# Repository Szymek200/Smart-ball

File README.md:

# ⚽ SmartBall: IoT Sports Training System

SmartBall is a comprehensive hardware and software solution designed to enhance sports training by monitoring ball dynamics in real-time. The system focuses on tracking impact force and spin (angular velocity), providing athletes with immediate feedback on their performance.

This project was developed as part of the "Microprocessor and Embedded Systems" course at the Silesian University of Technology (Politechnika Śląska).

## 📂 Repository Structure

This repository is organized into three specialized modules. For detailed technical instructions and implementation logic, please refer to the documentation within each folder:

* **/mobile-app** – Android application (Kotlin) for real-time UDP data visualization, session history, and remote sensor configuration.
* **/firmware-esp32** – ESP-IDF C code featuring high-G impact detection, quaternion-based sensor fusion (complementary filter), and power management.
* **/hardware-3d** – 3D enclosure designs (PET-G), PCB schematics, and the Bill of Materials (BOM).

## ⚙️ System Architecture

The system utilizes a **Producer-Consumer** architecture to ensure high performance and low latency:

* **The Producer (ESP32):** Equipped with an **H3LIS331DL** (400g accelerometer) and an **L3G4200D** (2000 dps gyroscope). It processes raw motion data, compensates for gravity using quaternions, and detects strikes using a circular buffer to capture pre-impact telemetry.
* **The Consumer (Mobile App):** Connects to the ball via a Wi-Fi Access Point and receives processed statistics and live streams using a high-speed binary UDP protocol.

## 🚀 Quick Start Guide

1.  **Power On:** Ensure the Li-Pol battery is charged and the device is powered.
2.  **Connect Wi-Fi:** On your mobile device, connect to the SmartBall network:
    * **SSID:** `SmartBall_ESP32`
    * **Password:** `12345678`
3.  **Launch Application:** Open the SmartBall app to begin receiving data.
4.  **Analyze:** Use the "History" section to view detailed charts of every kick, including G-force and rotation speed.

## 🔋 Power Management

To maximize the 18-hour battery life, the system includes an automated Power Management Algorithm:
* **Deep Sleep:** The MCU enters deep sleep after a configurable period of inactivity.
* **Motion Wake-up:** The accelerometer remains active as a low-power motion detector, waking the ESP32 via a hardware interrupt (GPIO 32) when the ball is moved.

## 🛠 Tech Stack Summary

* **Microcontroller:** ESP32-WROOM-32 (Dual-core).
* **Firmware:** ESP-IDF (C), FreeRTOS, LwIP (UDP).
* **Mobile App:** Kotlin, Coroutines, MPAndroidChart.
* **Mechanical:** 3D Printed PET-G, Li-Pol 1580mAh, MP2636 Power Manager.

---
*Developed by Szymon Mamok | Silesian University of Technology 2025/2026*

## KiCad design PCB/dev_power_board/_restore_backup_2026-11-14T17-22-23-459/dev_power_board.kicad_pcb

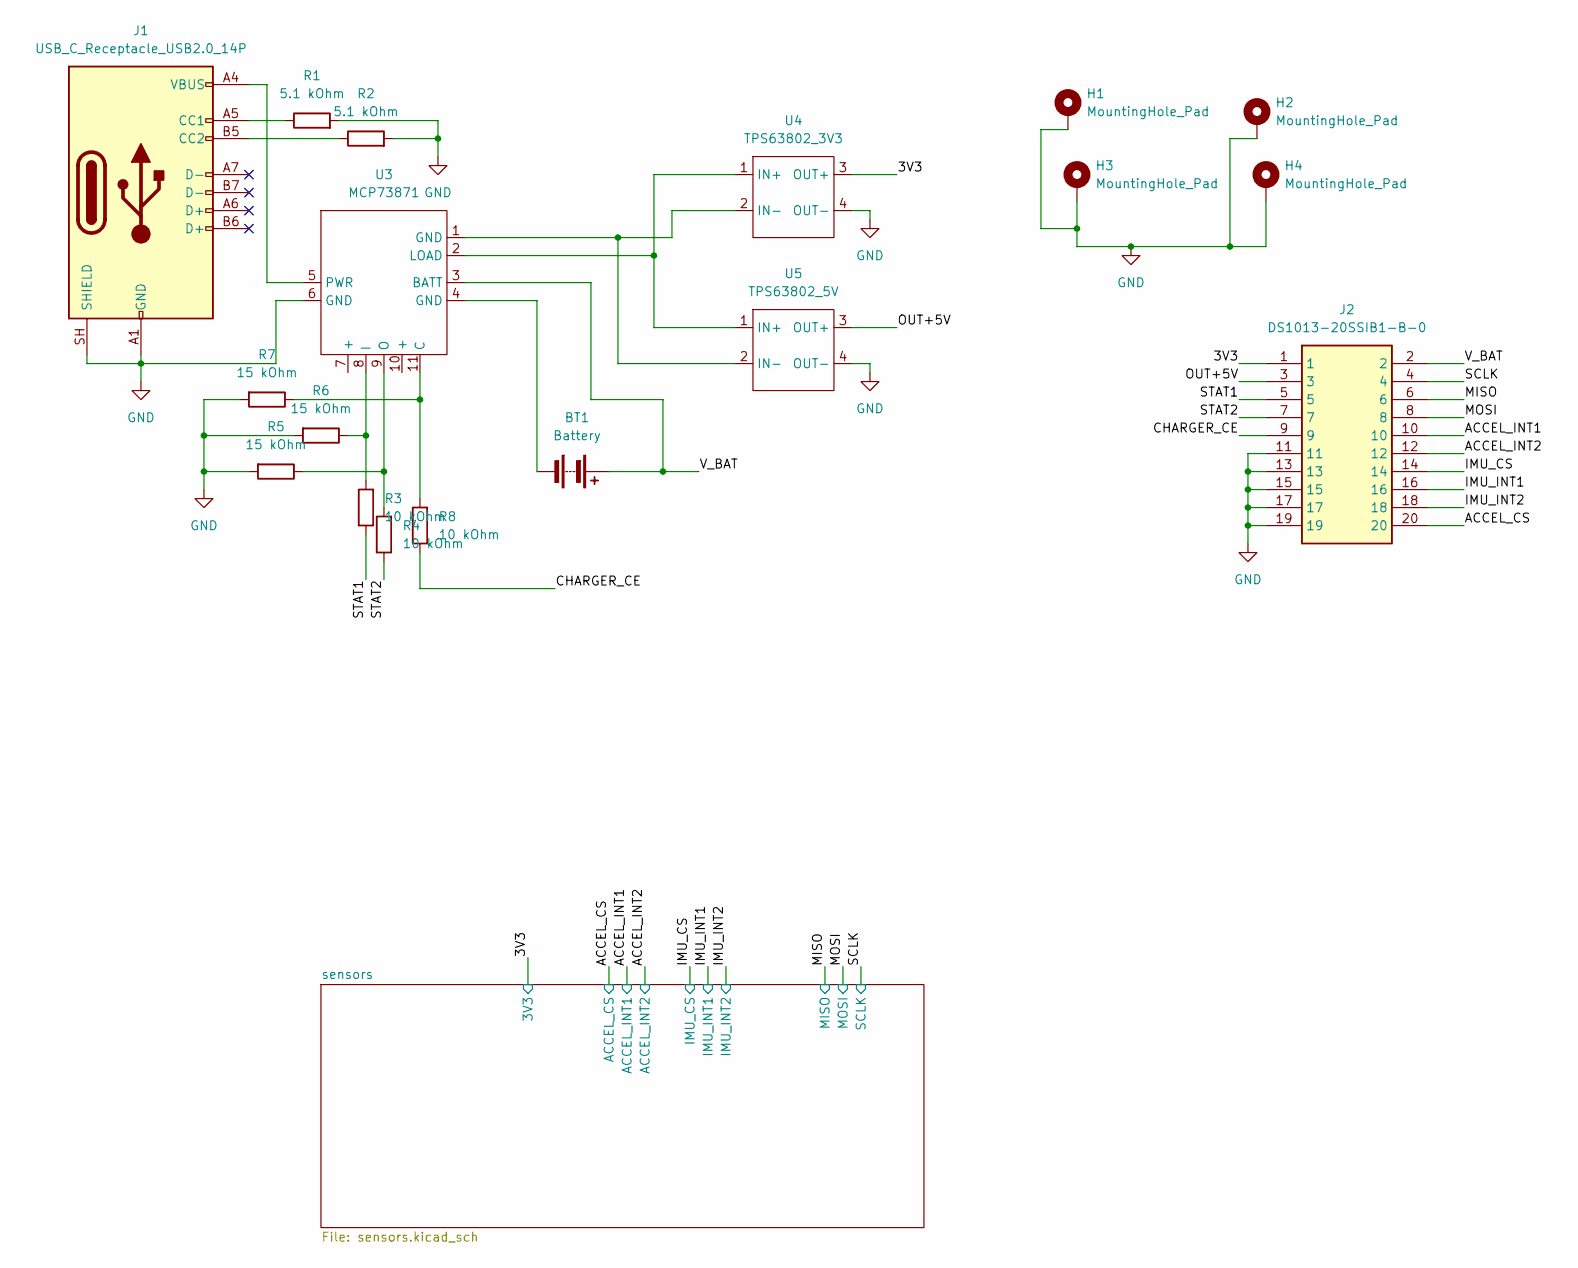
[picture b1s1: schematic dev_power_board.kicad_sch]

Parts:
BT1: Battery; PinHeader_1x02_P2.54mm_Vertical
H1, H2, H3, H4: MountingHole_Pad; MountingHole_2.2mm_M2_Pad
J1: USB_C_Receptacle_USB2.0_14P; USB_C_Receptacle_HRO_TYPE-C-31-M-12
J2: DS1013-20SSIB1-B-0; SHDR20W69P254X254_2X10_3300X910X955P; Manufacturer_Part_Number DS1013-20SSIB1-B-0
R1, R2: 5.1 kOhm; R_Axial_DIN0207_L6.3mm_D2.5mm_P7.62mm_Horizontal
R3, R4, R8: 10 kOhm; R_Axial_DIN0207_L6.3mm_D2.5mm_P7.62mm_Horizontal
R5, R6, R7: 15 kOhm; R_Axial_DIN0207_L6.3mm_D2.5mm_P7.62mm_Horizontal
U3: MCP73871; MCP73871_dev
U4: TPS63802_3V3; TPS63802_dev
U5: TPS63802_5V; TPS63802_dev

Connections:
/3V3: J2.1, U4.3 (OUT+); also elsewhere on the board
/ACCEL_CS: J2.20; also elsewhere on the board
/ACCEL_INT1: J2.10; also elsewhere on the board
/ACCEL_INT2: J2.12; also elsewhere on the board
/CHARGER_CE: J2.9, R8.1
/IMU_CS: J2.14; also elsewhere on the board
/IMU_INT1: J2.16; also elsewhere on the board
/IMU_INT2: J2.18; also elsewhere on the board
/MISO: J2.6; also elsewhere on the board
/MOSI: J2.8; also elsewhere on the board
/OUT+5V: J2.3, U5.3 (OUT+)
/SCLK: J2.4; also elsewhere on the board
/STAT1: J2.5, R3.1
/STAT2: J2.7, R4.1
/V_BAT: BT1.1 (+), J2.2, U3.3 (BATT)
GND: H1.1 (1_1), H2.1 (1_1), H3.1 (1_1), H4.1 (1_1), J1.A1 (GND), J1.A12 (GND), J1.B1 (GND), J1.B12 (GND), J1.SH (SHIELD), J2.11, J2.13, J2.15, J2.17, J2.19, R1.2, R2.2, R5.2, R6.2, R7.2, U3.6 (GND), U4.4 (OUT-), U5.4 (OUT-); also elsewhere on the board
unnamed: BT1.2 (-), U3.4 (GND)
unnamed: J1.A5 (CC1), R1.1
unnamed: J1.B5 (CC2), R2.1
unnamed: R7.1, R8.2, U3.11 (C)
unnamed: R3.2, R6.1, U3.8 (I)
unnamed: U3.2 (LOAD), U4.1 (IN+), U5.1 (IN+)
unnamed: R4.2, R5.1, U3.9 (O)
unnamed: J1.A4 (VBUS), J1.A9 (VBUS), J1.B4 (VBUS), J1.B9 (VBUS), U3.5 (PWR)
unnamed: U3.1 (GND), U4.2 (IN-), U5.2 (IN-)

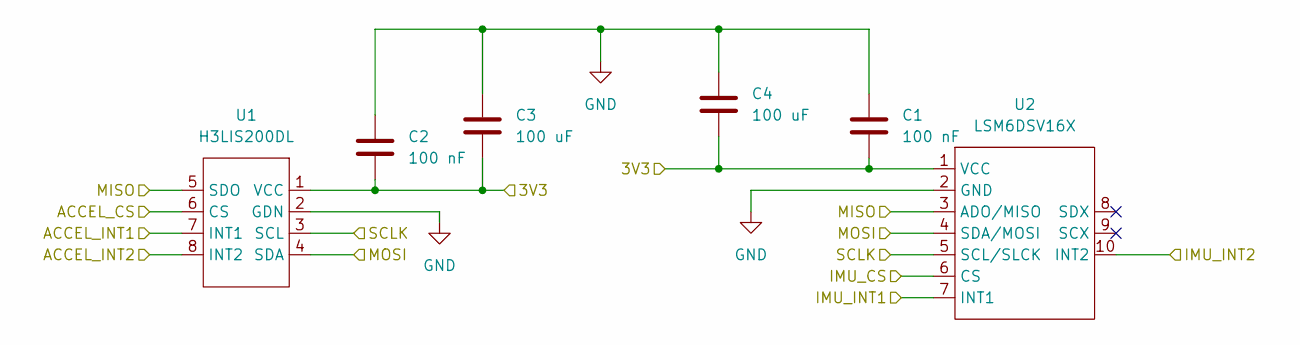
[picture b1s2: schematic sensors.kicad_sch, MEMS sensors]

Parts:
C1, C2: 100 nF; C_Disc_D5.0mm_W2.5mm_P5.00mm
C3, C4: 100 uF; CP_Radial_D6.3mm_P2.50mm
U1: H3LIS200DL; H3LIS200DL_dev
U2: LSM6DSV16X; LSM6DSV16X_dev

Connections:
/3V3: C1.2, C2.2, C3.1, C4.1, U1.1 (VCC), U2.1 (VCC); also elsewhere on the board
/ACCEL_CS: U1.6 (CS); also elsewhere on the board
/ACCEL_INT1: U1.7 (INT1); also elsewhere on the board
/ACCEL_INT2: U1.8 (INT2); also elsewhere on the board
/IMU_CS: U2.6 (CS); also elsewhere on the board
/IMU_INT1: U2.7 (INT1); also elsewhere on the board
/IMU_INT2: U2.10 (INT2); also elsewhere on the board
/MISO: U1.5 (SDO), U2.3 (ADO/MISO); also elsewhere on the board
/MOSI: U1.4 (SDA), U2.4 (SDA/MOSI); also elsewhere on the board
/SCLK: U1.3 (SCL), U2.5 (SCL/SLCK); also elsewhere on the board
GND: C1.1, C2.1, C3.2, C4.2, U1.2 (GDN), U2.2 (GND); also elsewhere on the board

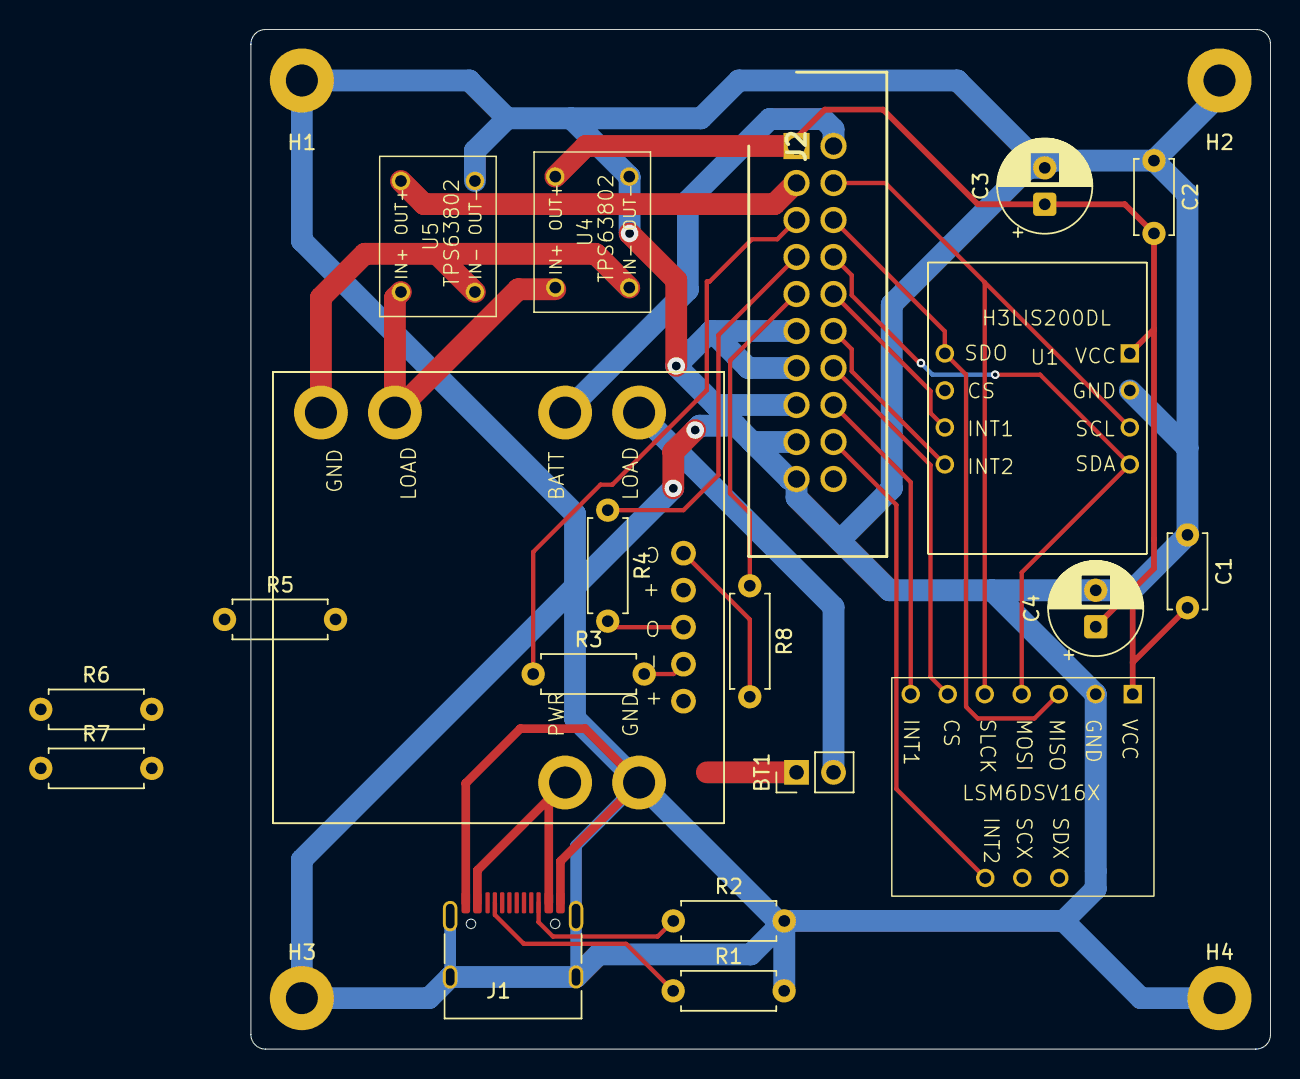
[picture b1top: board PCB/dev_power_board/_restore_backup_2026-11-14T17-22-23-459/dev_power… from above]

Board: 2 copper layers, 70.0 x 70.0 mm, 24 parts (0 on the bottom side), 25 nets.

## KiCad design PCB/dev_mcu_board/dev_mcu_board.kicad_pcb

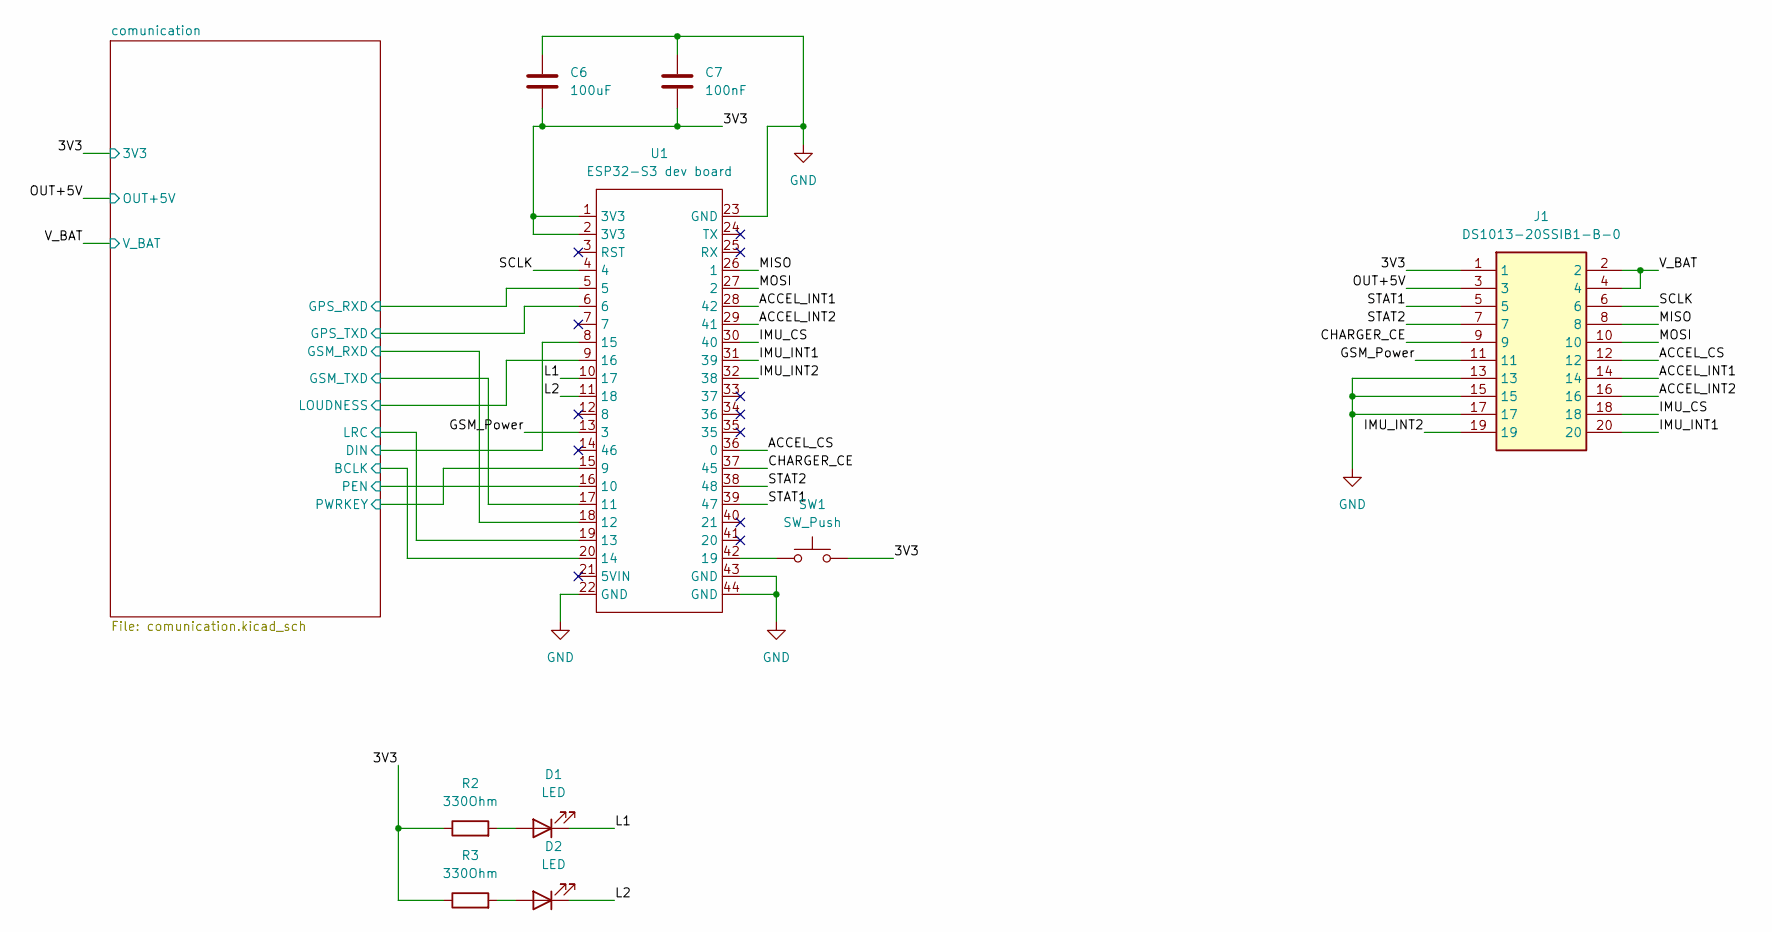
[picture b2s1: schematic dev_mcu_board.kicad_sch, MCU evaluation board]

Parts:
C6: 100uF; CP_Radial_D6.3mm_P2.50mm
C7: 100nF; C_Disc_D5.0mm_W2.5mm_P5.00mm
D1, D2: LED; LED_D5.0mm
J1: DS1013-20SSIB1-B-0; SHDR20W69P254X254_2X10_3300X910X955P; Manufacturer_Part_Number DS1013-20SSIB1-B-0
R2, R3: 330Ohm; R_Axial_DIN0207_L6.3mm_D2.5mm_P7.62mm_Horizontal
SW1: SW_Push; push_button
U1: ESP32-S3 dev board; esp32-s3_dev

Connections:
/3V3: C6.1, C7.2, J1.1, R2.1, R3.1, SW1.2, U1.1 (3V3), U1.2 (3V3); also elsewhere on the board
/ACCEL_CS: J1.12, U1.36 (0)
/ACCEL_INT1: J1.14, U1.28 (42)
/ACCEL_INT2: J1.16, U1.29 (41)
/CHARGER_CE: J1.9, U1.37 (45)
/GSM_Power: J1.11, U1.13 (3)
/IMU_CS: J1.18, U1.30 (40)
/IMU_INT1: J1.20, U1.31 (39)
/IMU_INT2: J1.19, U1.32 (38)
/L1: D1.1 (K), U1.10 (17)
/L2: D2.1 (K), U1.11 (18)
/MISO: J1.8, U1.26 (1)
/MOSI: J1.10, U1.27 (2)
/OUT+5V: J1.3; also elsewhere on the board
/SCLK: J1.6, U1.4
/STAT1: J1.5, U1.39 (47)
/STAT2: J1.7, U1.38 (48)
/V_BAT: J1.2, J1.4; also elsewhere on the board
/comunication/BCLK: U1.20 (14); also elsewhere on the board
/comunication/DIN: U1.8 (15); also elsewhere on the board
/comunication/GPS_RXD: U1.5; also elsewhere on the board
/comunication/GPS_TXD: U1.6; also elsewhere on the board
/comunication/GSM_RXD: U1.18 (12); also elsewhere on the board
/comunication/GSM_TXD: U1.17 (11); also elsewhere on the board
/comunication/LOUDNESS: U1.9 (16); also elsewhere on the board
/comunication/LRC: U1.19 (13); also elsewhere on the board
/comunication/PEN: U1.16 (10); also elsewhere on the board
/comunication/PWRKEY: U1.15 (9); also elsewhere on the board
GND: C6.2, C7.1, J1.13, J1.15, J1.17, U1.22 (GND), U1.23 (GND), U1.43 (GND), U1.44 (GND); also elsewhere on the board
unnamed: D1.2 (A), R2.2
unnamed: D2.2 (A), R3.2
unnamed: SW1.1, U1.42 (19)

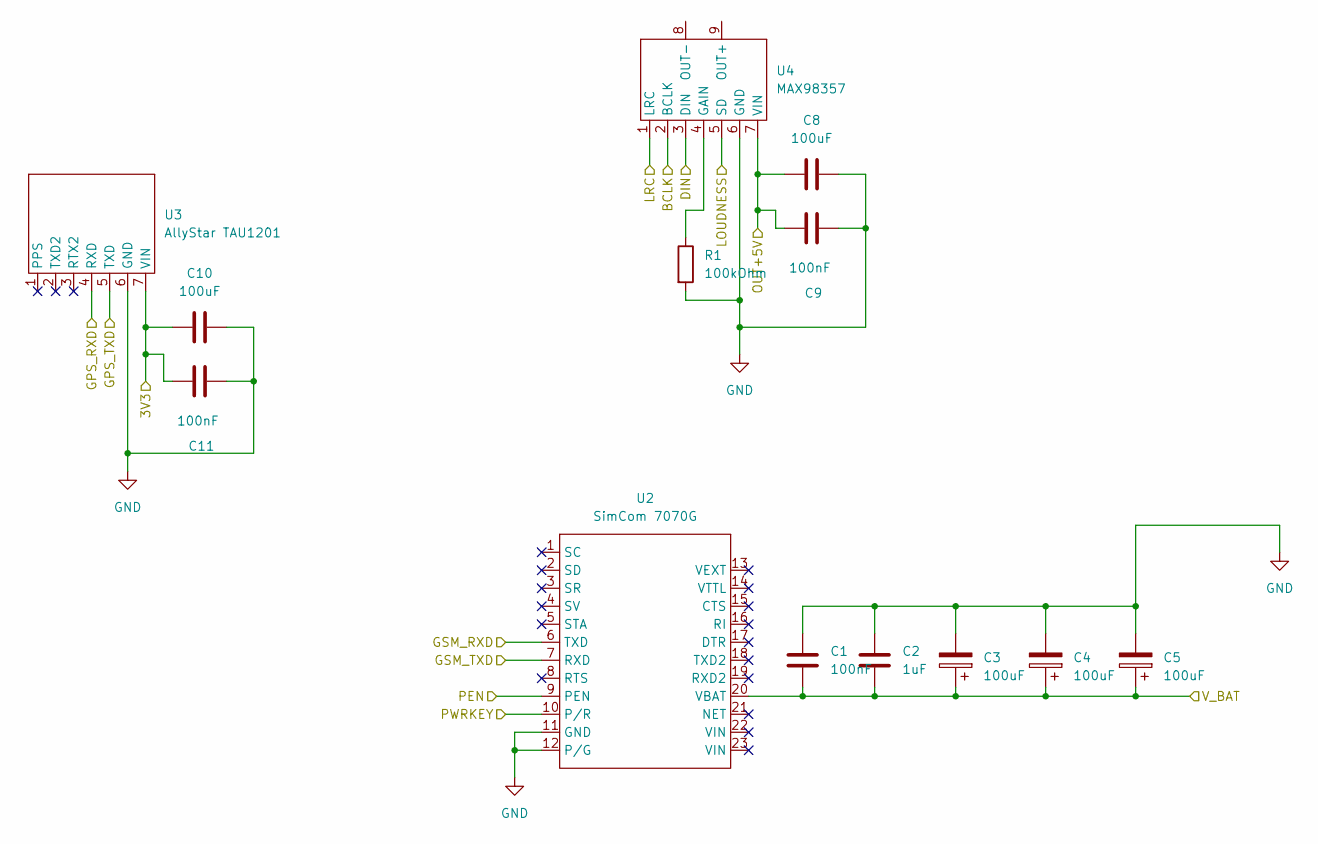
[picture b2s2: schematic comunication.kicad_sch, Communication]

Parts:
C1, C9, C11: 100nF; C_Disc_D5.0mm_W2.5mm_P5.00mm
C2: 1uF; CP_Radial_D5.0mm_P2.00mm
C3, C4, C5, C8, C10: 100uF; CP_Radial_D6.3mm_P2.50mm
R1: 100kOhm; R_Axial_DIN0207_L6.3mm_D2.5mm_P7.62mm_Horizontal
U2: SimCom 7070G; sim7070G_dev
U3: AllyStar TAU1201; TAU1201_dev
U4: MAX98357; MAX98357_dev

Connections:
/3V3: C10.1, C11.1, U3.7 (VIN); also elsewhere on the board
/OUT+5V: C8.1, C9.1, U4.7 (VIN); also elsewhere on the board
/V_BAT: C1.2, C2.1, C3.1, C4.1, C5.1, U2.20 (VBAT); also elsewhere on the board
/comunication/BCLK: U4.2 (BCLK); also elsewhere on the board
/comunication/DIN: U4.3 (DIN); also elsewhere on the board
/comunication/GPS_RXD: U3.4 (RXD); also elsewhere on the board
/comunication/GPS_TXD: U3.5 (TXD); also elsewhere on the board
/comunication/GSM_RXD: U2.6 (TXD); also elsewhere on the board
/comunication/GSM_TXD: U2.7 (RXD); also elsewhere on the board
/comunication/LOUDNESS: U4.5 (SD); also elsewhere on the board
/comunication/LRC: U4.1 (LRC); also elsewhere on the board
/comunication/PEN: U2.9 (PEN); also elsewhere on the board
/comunication/PWRKEY: U2.10 (P/R); also elsewhere on the board
GND: C1.1, C2.2, C3.2, C4.2, C5.2, C8.2, C9.2, C10.2, C11.2, R1.2, U2.11 (GND), U2.12 (P/G), U3.6 (GND), U4.6 (GND); also elsewhere on the board
unnamed: R1.1, U4.4 (GAIN)

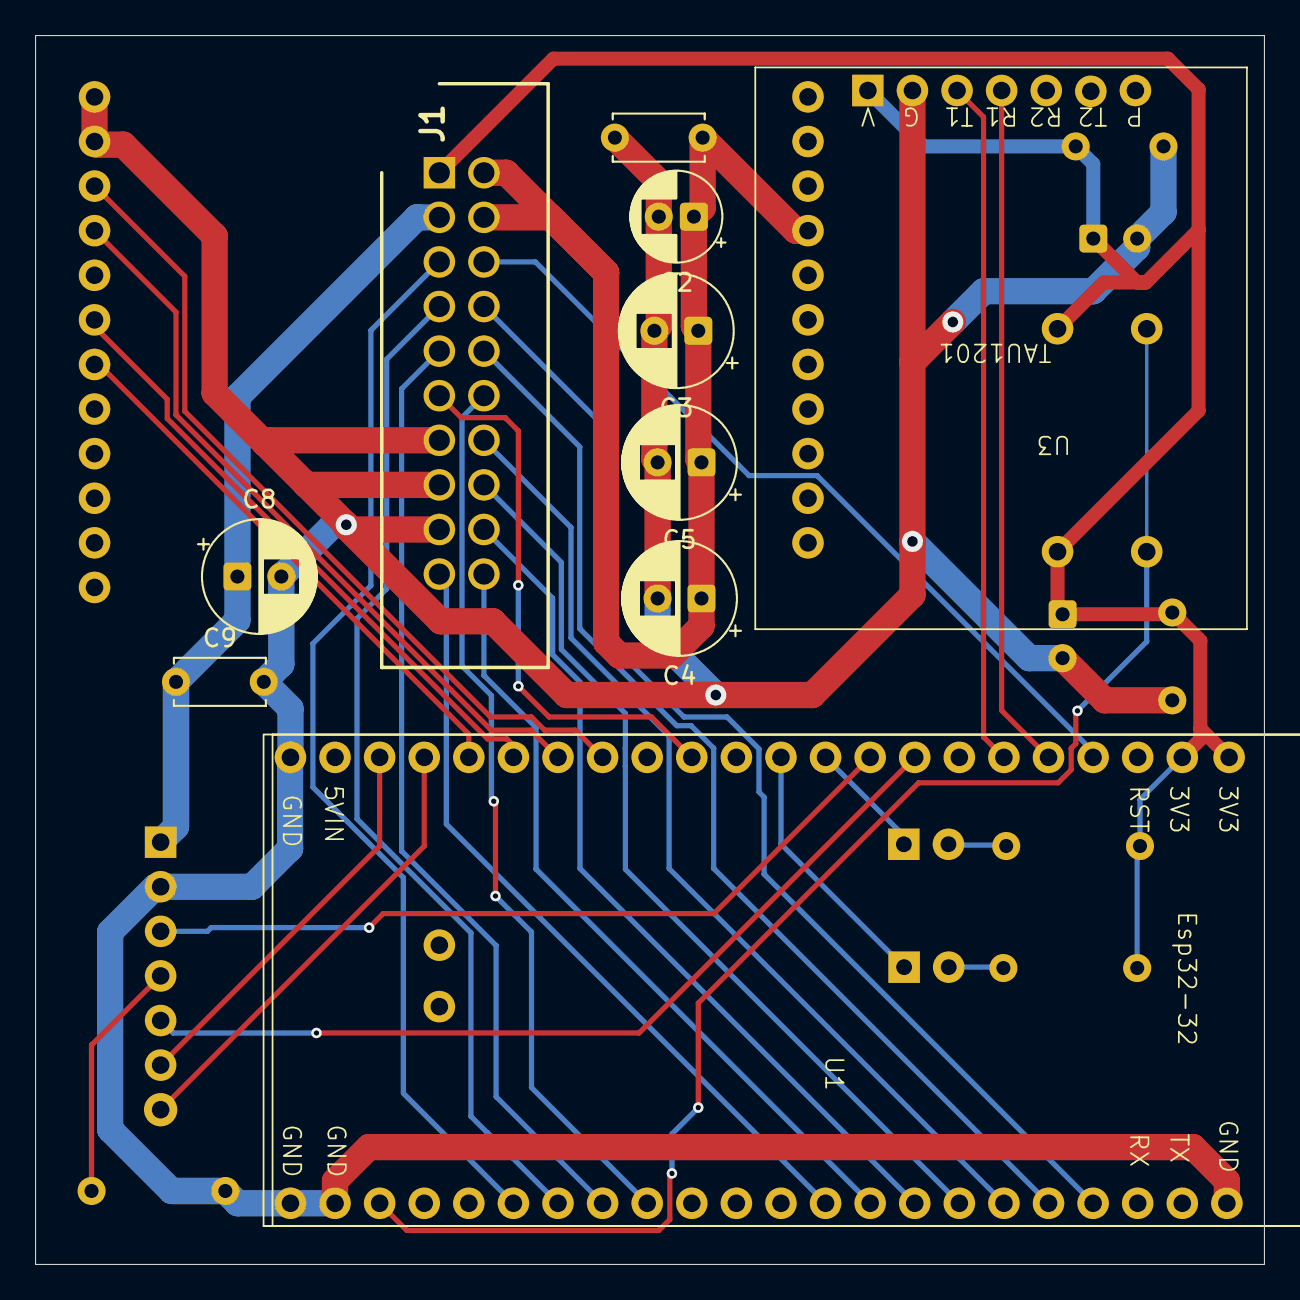
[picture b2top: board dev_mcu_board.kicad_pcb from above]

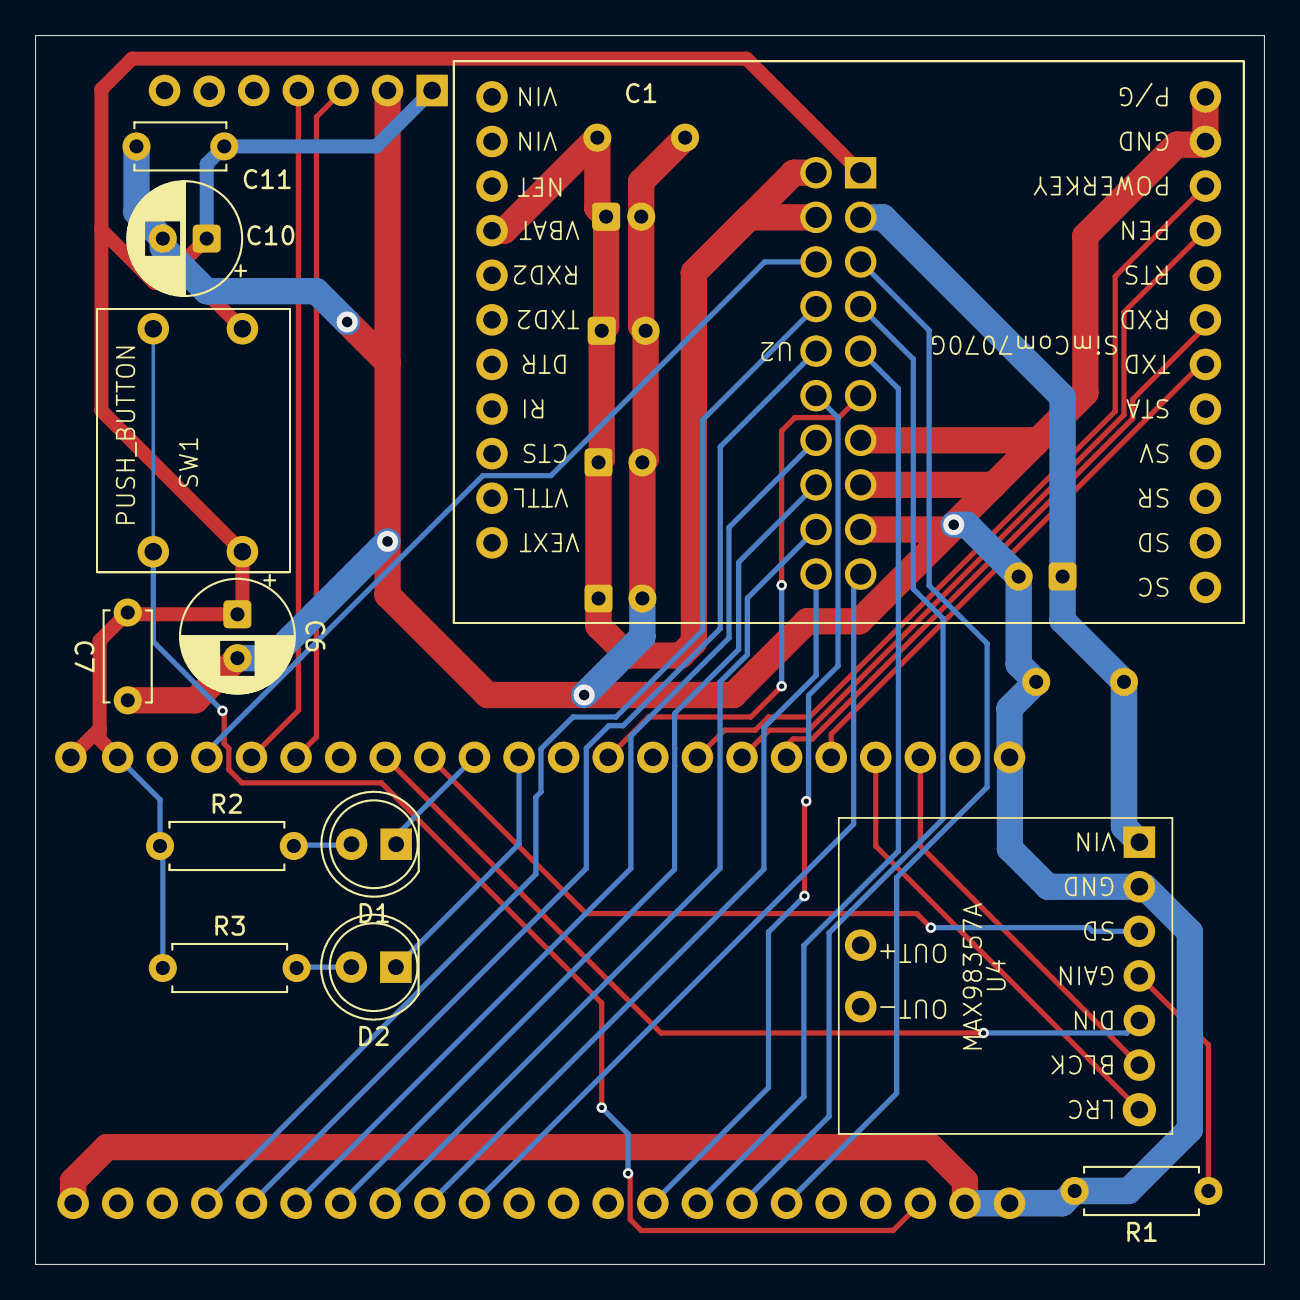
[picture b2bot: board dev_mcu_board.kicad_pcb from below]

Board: 2 copper layers, 70.0 x 70.0 mm, 22 parts (12 on the bottom side), 33 nets.

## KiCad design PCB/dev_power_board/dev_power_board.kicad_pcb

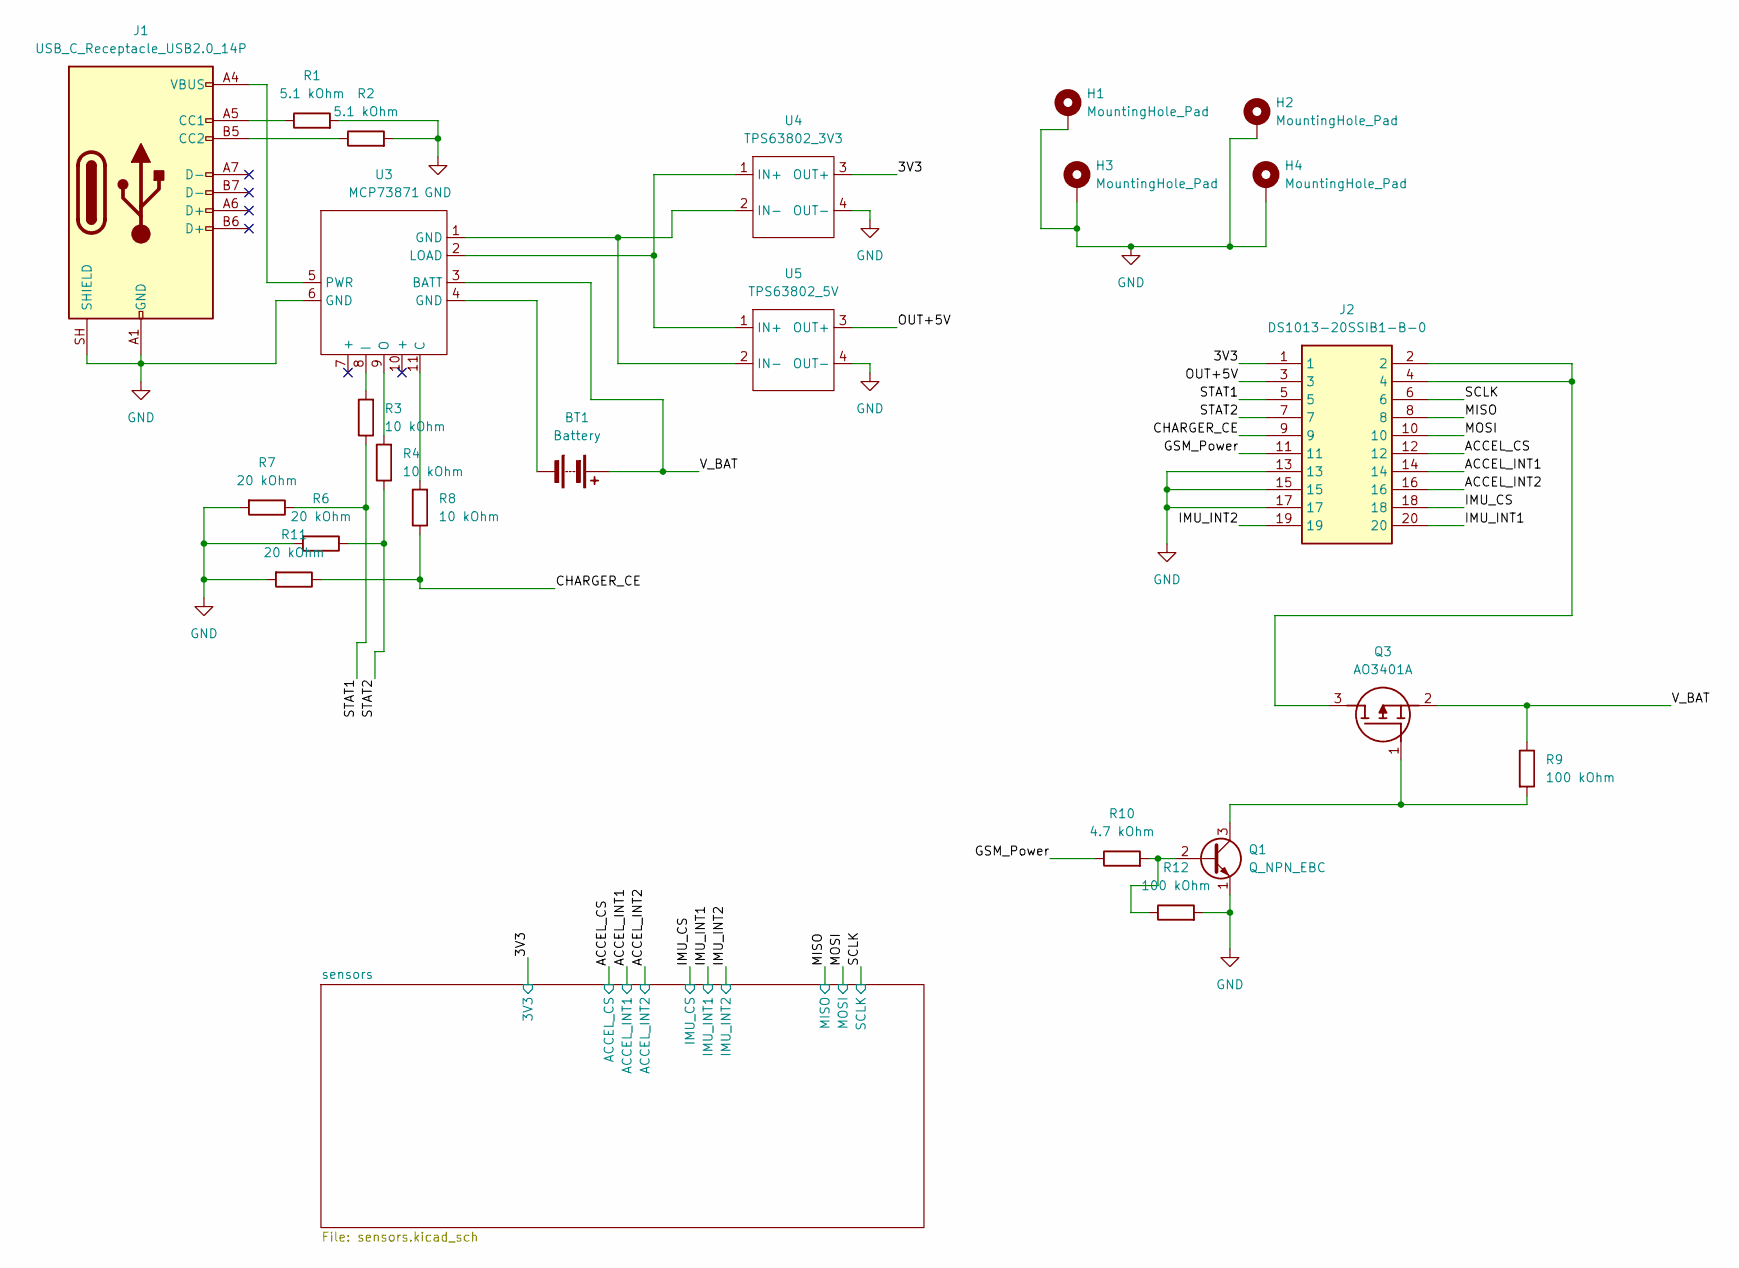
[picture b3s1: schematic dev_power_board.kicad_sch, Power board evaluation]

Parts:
BT1: Battery; PinHeader_1x02_P2.54mm_Vertical
H1, H2, H3, H4: MountingHole_Pad; MountingHole_2.2mm_M2_Pad
J1: USB_C_Receptacle_USB2.0_14P; USB_C_Receptacle_HRO_TYPE-C-31-M-12
J2: DS1013-20SSIB1-B-0; SHDR20W69P254X254_2X10_3300X910X955P; Manufacturer_Part_Number DS1013-20SSIB1-B-0
Q1: Q_NPN_EBC; TO-92_Wide
Q3: AO3401A; SOT95P280X125-3N; Manufacturer_Part_Number AO3401A
R1, R2: 5.1 kOhm; R_Axial_DIN0207_L6.3mm_D2.5mm_P7.62mm_Horizontal
R3, R4, R8: 10 kOhm; R_Axial_DIN0207_L6.3mm_D2.5mm_P7.62mm_Horizontal
R6, R7, R11: 20 kOhm; R_Axial_DIN0207_L6.3mm_D2.5mm_P7.62mm_Horizontal
R9, R12: 100 kOhm; R_Axial_DIN0207_L6.3mm_D2.5mm_P7.62mm_Horizontal
R10: 4.7 kOhm; R_Axial_DIN0207_L6.3mm_D2.5mm_P7.62mm_Horizontal
U3: MCP73871; MCP73871_dev
U4: TPS63802_3V3; TPS63802_dev
U5: TPS63802_5V; TPS63802_dev

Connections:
/3V3: J2.1, U4.3 (OUT+); also elsewhere on the board
/ACCEL_CS: J2.12; also elsewhere on the board
/ACCEL_INT1: J2.14; also elsewhere on the board
/ACCEL_INT2: J2.16; also elsewhere on the board
/CHARGER_CE: J2.9, R8.1, R11.1
/GSM_Power: J2.11, R10.1
/IMU_CS: J2.18; also elsewhere on the board
/IMU_INT1: J2.20; also elsewhere on the board
/IMU_INT2: J2.19; also elsewhere on the board
/MISO: J2.8; also elsewhere on the board
/MOSI: J2.10; also elsewhere on the board
/OUT+5V: J2.3, U5.3 (OUT+)
/SCLK: J2.6; also elsewhere on the board
/STAT1: J2.5, R3.1, R7.1
/STAT2: J2.7, R4.1, R6.1
/V_BAT: BT1.1 (+), Q3.2 (S), R9.1, U3.3 (BATT)
GND: H1.1 (1_1), H2.1 (1_1), H3.1 (1_1), H4.1 (1_1), J1.A1 (GND), J1.A12 (GND), J1.B1 (GND), J1.B12 (GND), J1.SH (SHIELD), J2.13, J2.15, J2.17, Q1.1 (E), R1.2, R2.2, R6.2, R7.2, R11.2, R12.2, U3.6 (GND), U4.4 (OUT-), U5.4 (OUT-); also elsewhere on the board
unnamed: BT1.2 (-), U3.4 (GND)
unnamed: J1.A5 (CC1), R1.1
unnamed: J1.B5 (CC2), R2.1
unnamed: Q1.2 (B), R10.2, R12.1
unnamed: Q1.3 (C), Q3.1 (G), R9.2
unnamed: J2.2, J2.4, Q3.3 (D)
unnamed: R8.2, U3.11 (C)
unnamed: R3.2, U3.8 (I)
unnamed: U3.2 (LOAD), U4.1 (IN+), U5.1 (IN+)
unnamed: R4.2, U3.9 (O)
unnamed: J1.A4 (VBUS), J1.A9 (VBUS), J1.B4 (VBUS), J1.B9 (VBUS), U3.5 (PWR)
unnamed: U3.1 (GND), U4.2 (IN-), U5.2 (IN-)

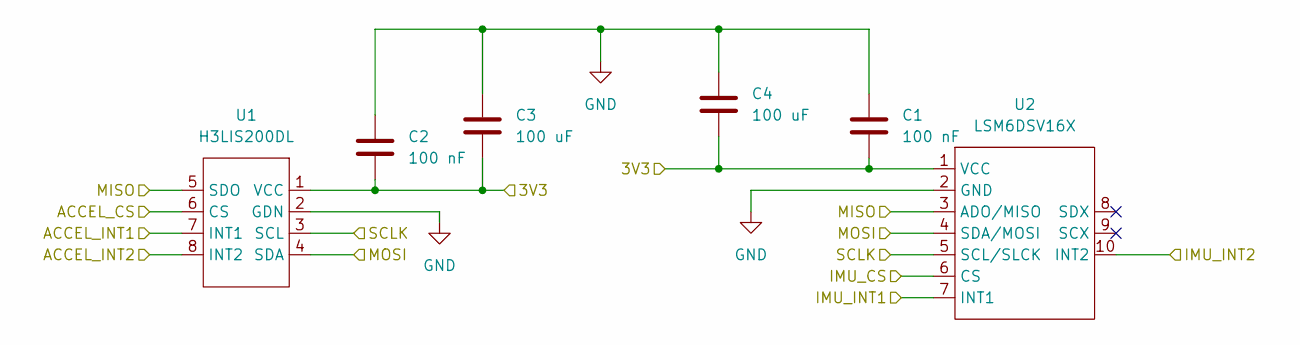
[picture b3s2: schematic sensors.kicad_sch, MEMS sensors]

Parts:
C1, C2: 100 nF; C_Disc_D5.0mm_W2.5mm_P5.00mm
C3, C4: 100 uF; CP_Radial_D6.3mm_P2.50mm
U1: H3LIS200DL; H3LIS200DL_dev
U2: LSM6DSV16X; LSM6DSV16X_dev

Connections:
/3V3: C1.2, C2.2, C3.1, C4.1, U1.1 (VCC), U2.1 (VCC); also elsewhere on the board
/ACCEL_CS: U1.6 (CS); also elsewhere on the board
/ACCEL_INT1: U1.7 (INT1); also elsewhere on the board
/ACCEL_INT2: U1.8 (INT2); also elsewhere on the board
/IMU_CS: U2.6 (CS); also elsewhere on the board
/IMU_INT1: U2.7 (INT1); also elsewhere on the board
/IMU_INT2: U2.10 (INT2); also elsewhere on the board
/MISO: U1.5 (SDO), U2.3 (ADO/MISO); also elsewhere on the board
/MOSI: U1.4 (SDA), U2.4 (SDA/MOSI); also elsewhere on the board
/SCLK: U1.3 (SCL), U2.5 (SCL/SLCK); also elsewhere on the board
GND: C1.1, C2.1, C3.2, C4.2, U1.2 (GDN), U2.2 (GND); also elsewhere on the board

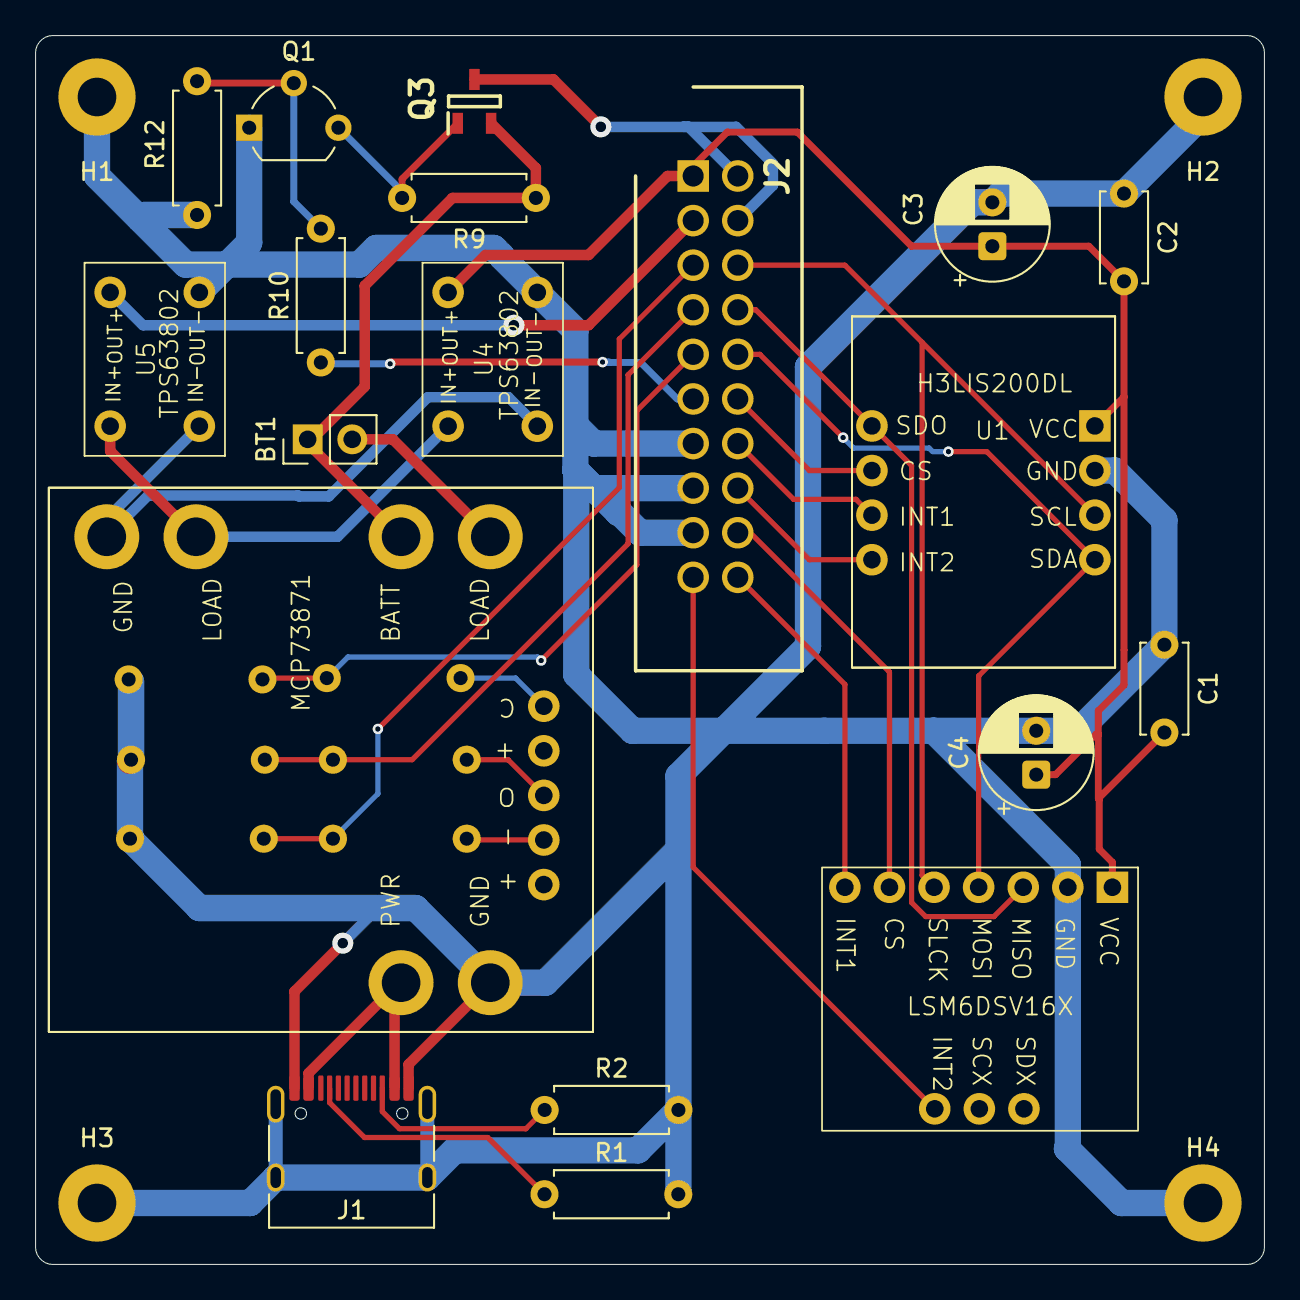
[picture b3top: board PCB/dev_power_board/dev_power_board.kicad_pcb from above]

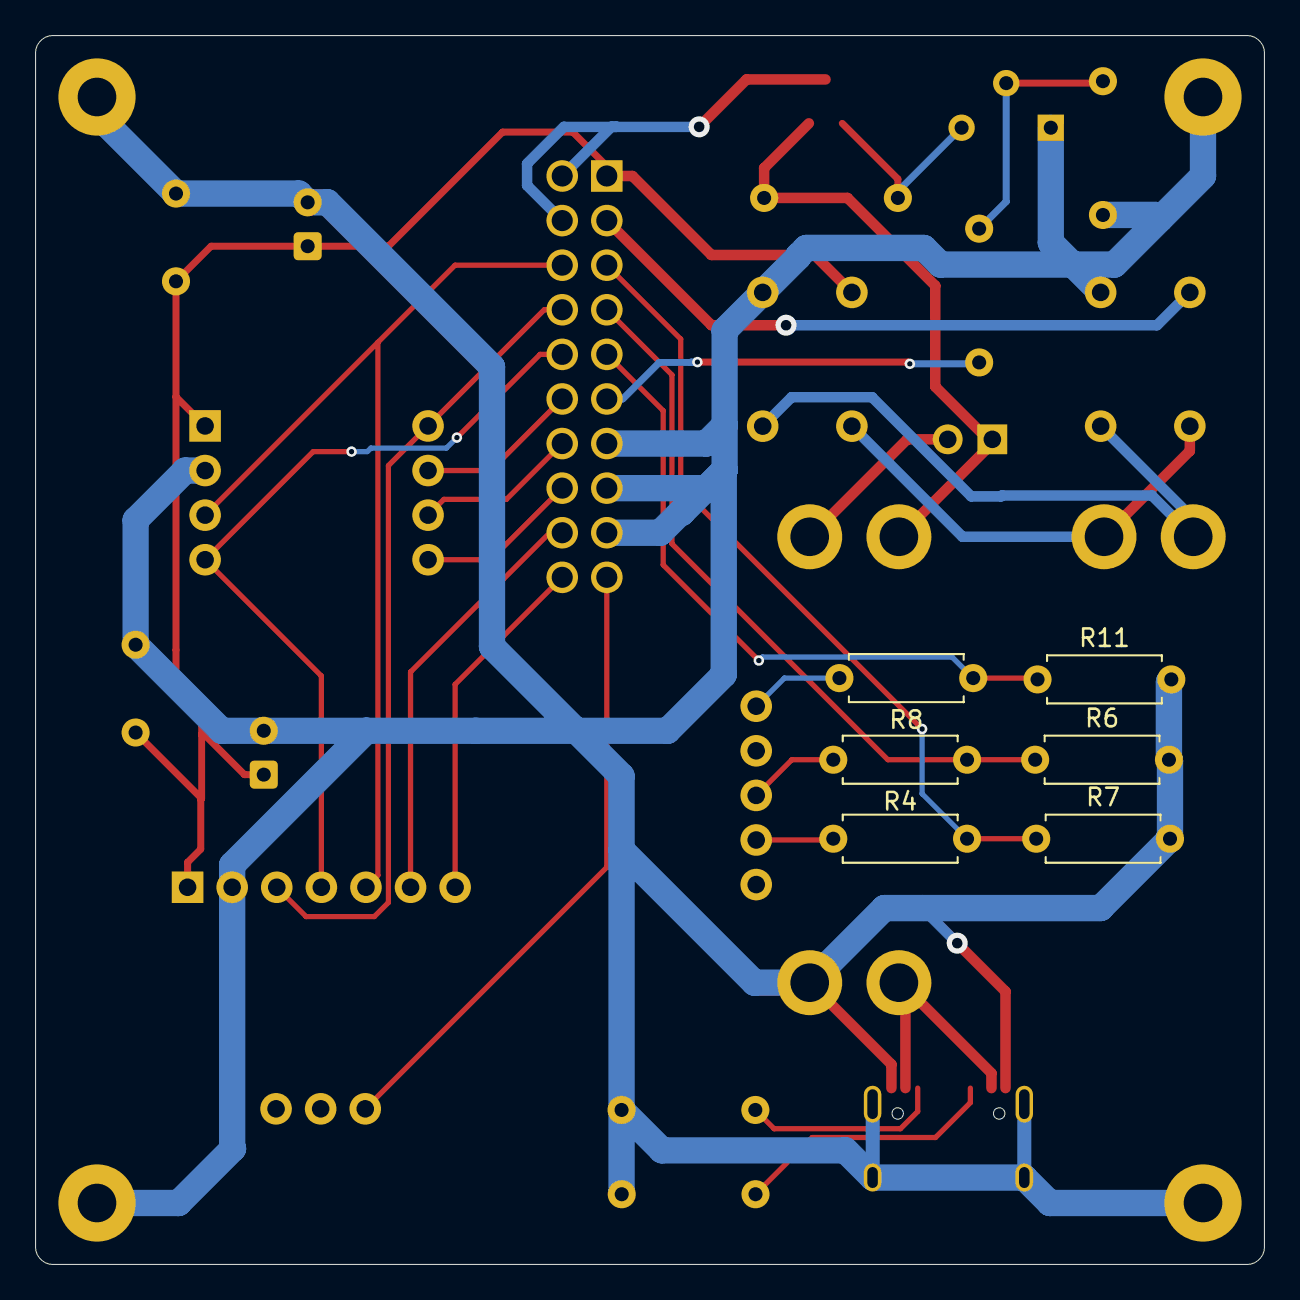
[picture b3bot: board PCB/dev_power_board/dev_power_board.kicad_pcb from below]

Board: 2 copper layers, 70.0 x 70.0 mm, 29 parts (6 on the bottom side), 29 nets.
